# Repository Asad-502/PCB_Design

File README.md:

# PCB_Design
 This repository will includes PCB Designs using Proteus,Altium and KiCAD

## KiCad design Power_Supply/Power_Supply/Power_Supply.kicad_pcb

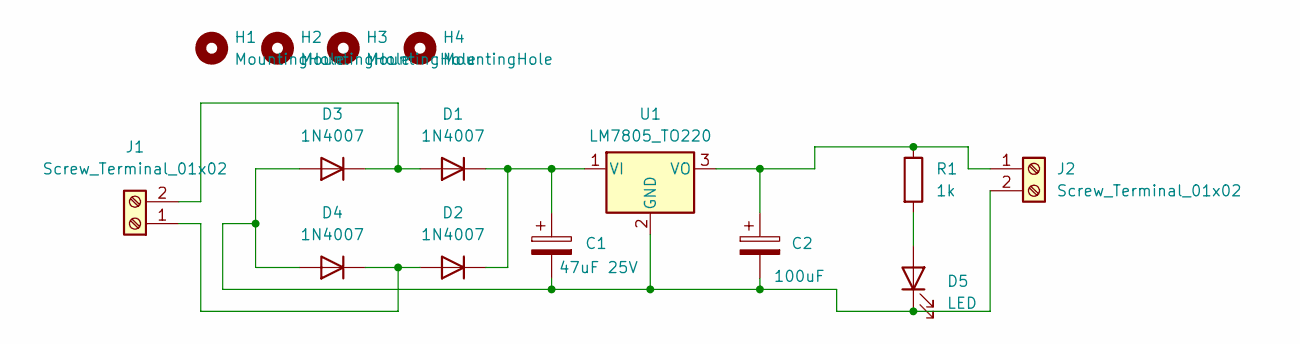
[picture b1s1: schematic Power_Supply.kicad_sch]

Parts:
C1: 47uF 25V; CP_Radial_D8.0mm_P3.80mm
C2: 100uF; CP_Radial_D8.0mm_P3.50mm
D1, D2, D3, D4: 1N4007; D_DO-41_SOD81_P10.16mm_Horizontal
D5: LED; LED_D3.0mm_Clear
H1, H2, H3, H4: MountingHole; MountingHole_2.2mm_M2_Pad_TopBottom
J1, J2: Screw_Terminal_01x02; TerminalBlock_bornier-2_P5.08mm
R1: 1k; R_Axial_DIN0204_L3.6mm_D1.6mm_P7.62mm_Horizontal
U1: LM7805_TO220; TO-220F-3_Vertical

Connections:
unnamed: D1.2 (A), D3.1 (K), J1.2
unnamed: C1.1, D1.1 (K), D2.1 (K), U1.1 (VI)
unnamed: D2.2 (A), D4.1 (K), J1.1
unnamed: C1.2, C2.2, D3.2 (A), D4.2 (A), D5.1 (K), J2.2, U1.2 (GND)
unnamed: D5.2 (A), R1.2
unnamed: C2.1, J2.1, R1.1, U1.3 (VO)

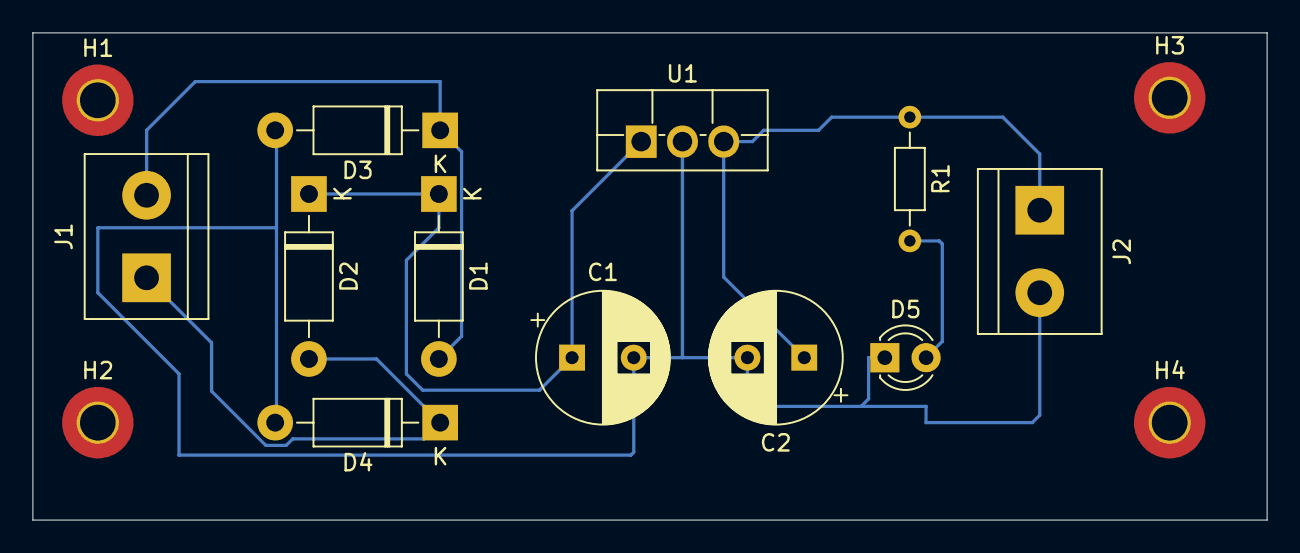
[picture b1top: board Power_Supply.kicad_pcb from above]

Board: 2 copper layers, 76.0 x 30.0 mm, 15 parts (0 on the bottom side), 6 nets.
